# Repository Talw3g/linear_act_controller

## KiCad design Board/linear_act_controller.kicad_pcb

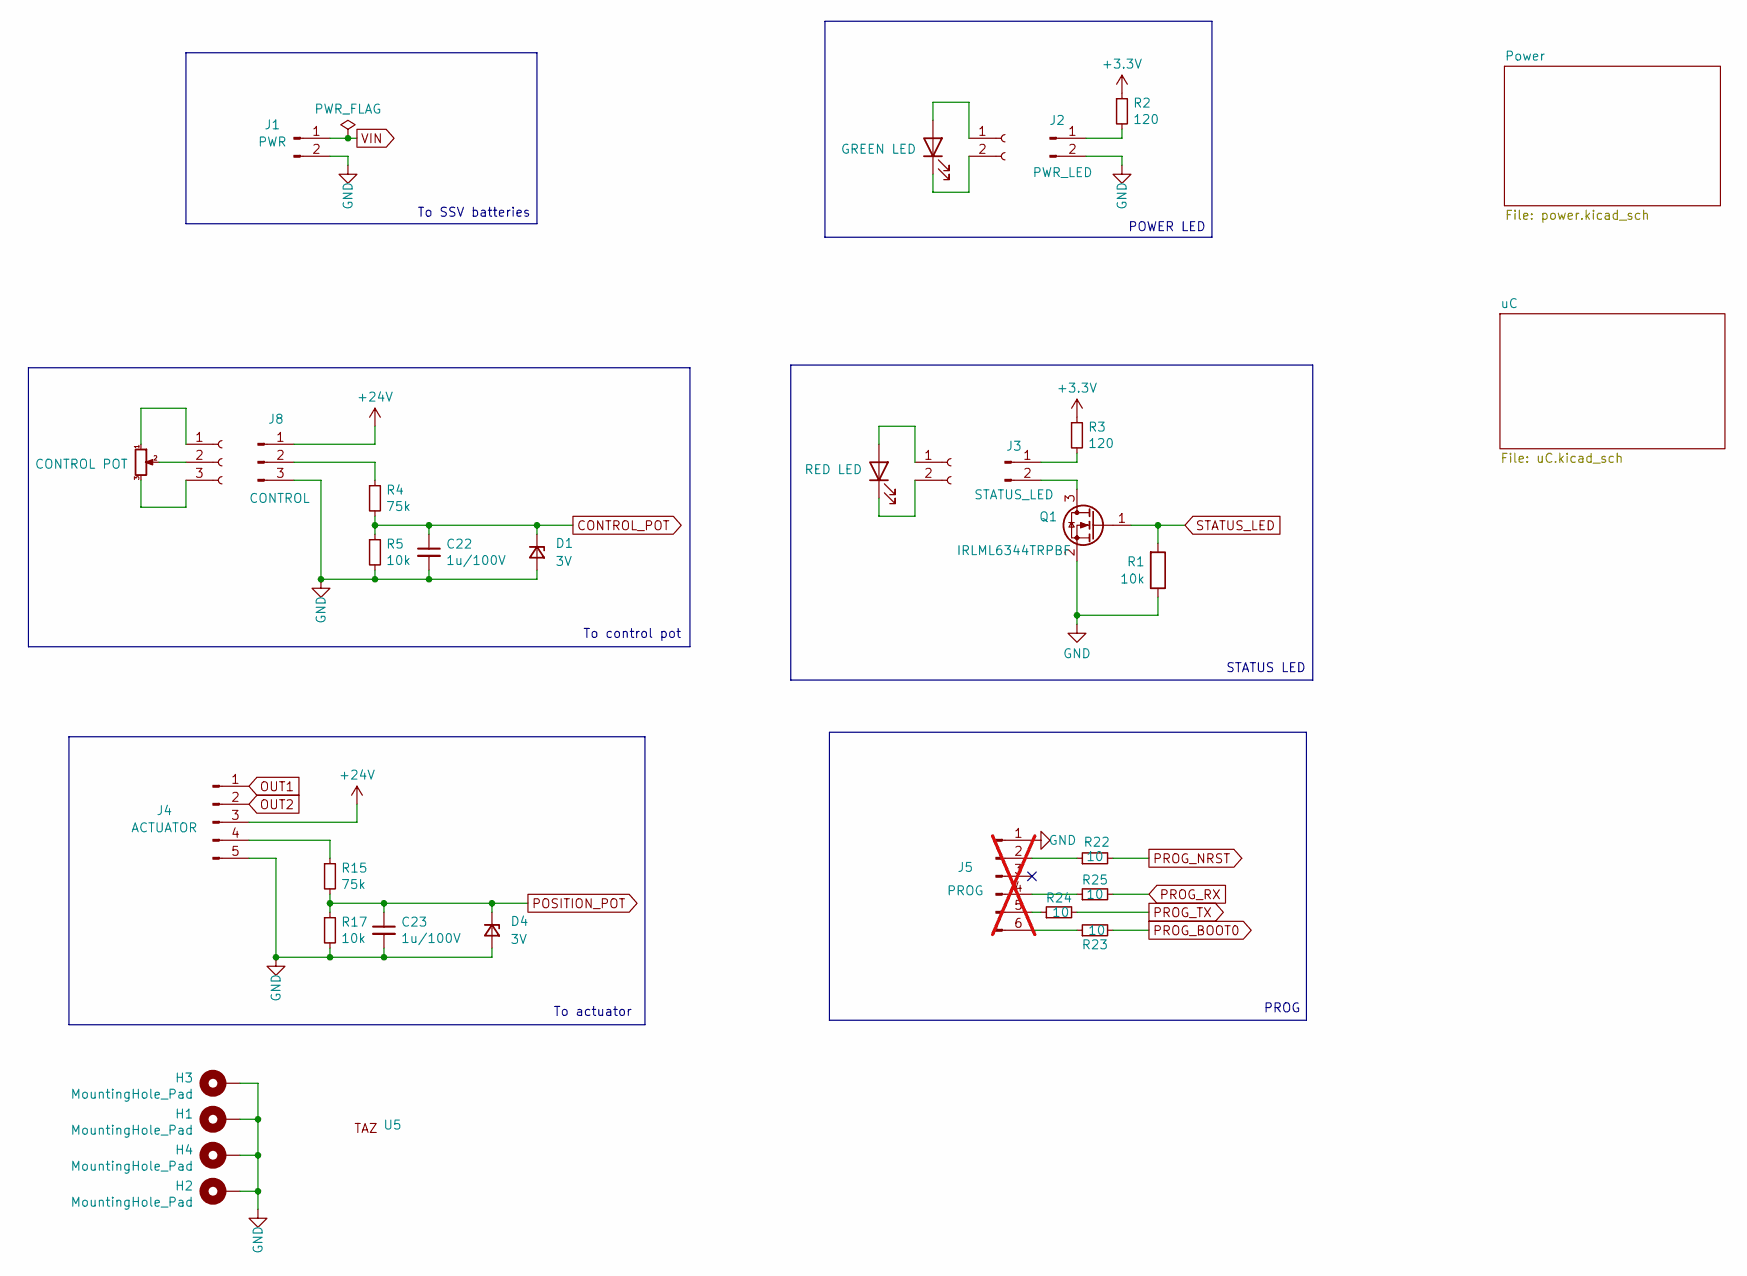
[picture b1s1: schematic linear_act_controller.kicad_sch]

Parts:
C22, C23: 1u/100V; C_0603_1608Metric_Pad1.08x0.95mm_HandSolder
D1, D4: 3V; D_SOD-323_HandSoldering
D6: GREEN LED
D7: RED LED
H1, H2, H3, H4: MountingHole_Pad; MountingHole_3.5mm_Pad_Via
J1: PWR; JST_XH_B2B-XH-A_1x02_P2.50mm_Vertical
J2: PWR_LED; JST_XH_B2B-XH-A_1x02_P2.50mm_Vertical
J3: STATUS_LED; JST_XH_B2B-XH-A_1x02_P2.50mm_Vertical
J4: ACTUATOR; JST_XH_B5B-XH-A_1x05_P2.50mm_Vertical
J5: PROG; 6pins_prog_header; not fitted
J6, J7: PWR_LED
J8: CONTROL; JST_XH_B3B-XH-A_1x03_P2.50mm_Vertical
J9: Conn_01x03_Socket
Q1: IRLML6344TRPBF; SOT-23
R1, R5, R17: 10k; R_0603_1608Metric_Pad0.98x0.95mm_HandSolder
R2, R3: 120; R_0603_1608Metric_Pad0.98x0.95mm_HandSolder
R4, R15: 75k; R_0603_1608Metric_Pad0.98x0.95mm_HandSolder
R22, R23, R24, R25: 10; R_0603_1608Metric_Pad0.98x0.95mm_HandSolder
RV1: CONTROL POT
U5: taz

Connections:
+3.3V: R2.1, R3.1; also elsewhere on the board
+24V: J4.3, J8.1; also elsewhere on the board
CONTROL_POT: C22.1, D1.1 (K), R4.2, R5.1; also elsewhere on the board
GND: C22.2, C23.2, D1.2 (A), D4.2 (A), H1.1, H2.1, H3.1, H4.1, J1.2, J2.2, J4.5, J5.1, J8.3, Q1.2 (S), R1.1, R5.2, R17.2; also elsewhere on the board
unnamed: D6.1 (K), J6.2
unnamed: D6.2 (A), J6.1
unnamed: D7.1 (K), J7.2
unnamed: D7.2 (A), J7.1
unnamed: J2.1, R2.2
unnamed: J3.1, R3.2
unnamed: J3.2, Q1.3 (D)
unnamed: J4.4, R15.1
unnamed: J5.2, R22.1
unnamed: J5.4, R25.1
unnamed: J5.5, R24.1
unnamed: J5.6, R23.1
unnamed: J8.2, R4.1
unnamed: J9.1, RV1.1
unnamed: J9.2, RV1.2
unnamed: J9.3, RV1.3
OUT1: J4.1; also elsewhere on the board
OUT2: J4.2; also elsewhere on the board
POSITION_POT: C23.1, D4.1 (K), R15.2, R17.1; also elsewhere on the board
PROG_BOOT0: R23.2; also elsewhere on the board
PROG_NRST: R22.2; also elsewhere on the board
PROG_RX: R25.2; also elsewhere on the board
PROG_TX: R24.2; also elsewhere on the board
STATUS_LED: Q1.1 (G), R1.2; also elsewhere on the board
VIN: J1.1; also elsewhere on the board

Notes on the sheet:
To control pot
STATUS LED
To actuator
To SSV batteries
POWER LED
PROG

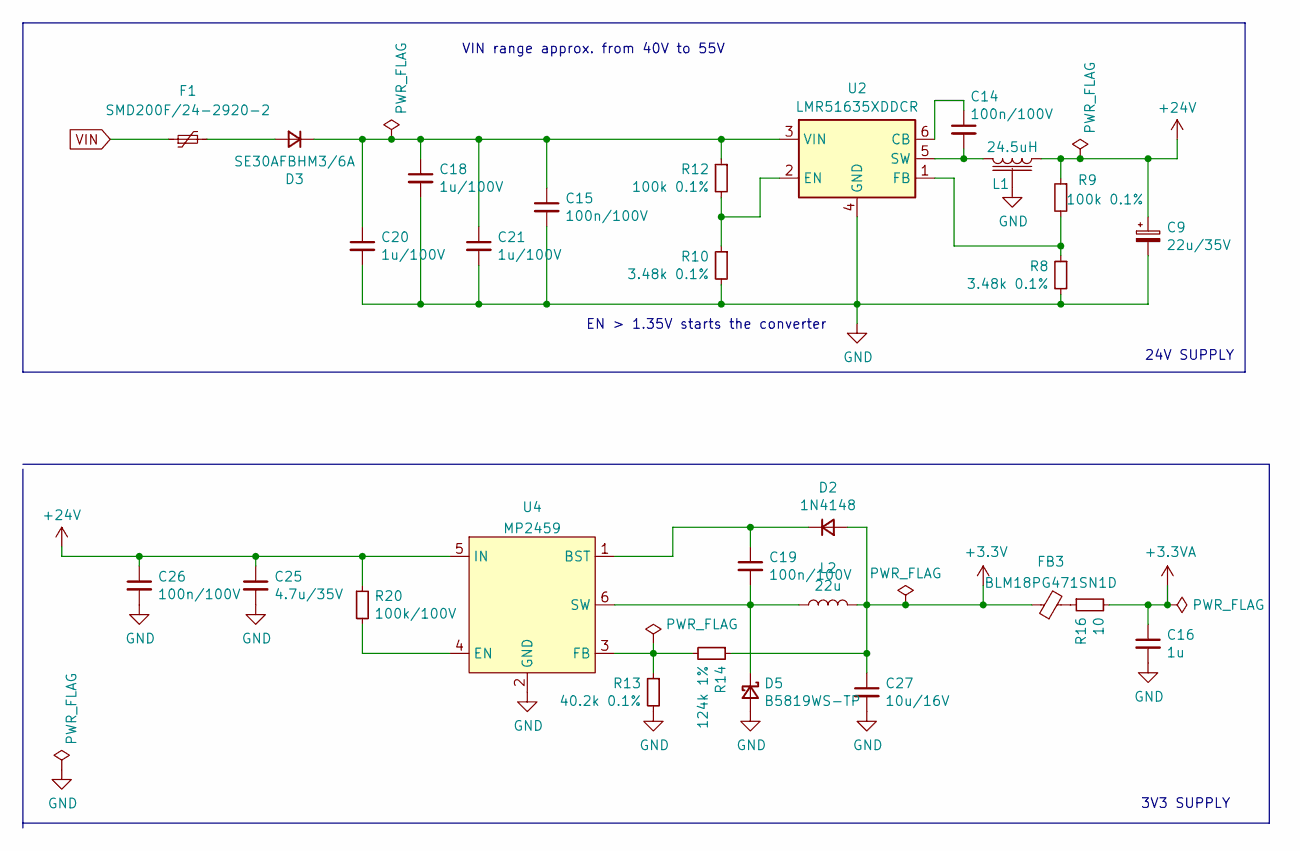
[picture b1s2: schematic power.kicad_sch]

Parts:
C9: 22u/35V; CP_Elec_6.3x5.8
C14, C15, C19, C26: 100n/100V; C_0603_1608Metric_Pad1.08x0.95mm_HandSolder
C16: 1u; C_0603_1608Metric_Pad1.08x0.95mm_HandSolder
C18, C20, C21: 1u/100V; C_0603_1608Metric_Pad1.08x0.95mm_HandSolder
C25: 4.7u/35V; C_0603_1608Metric_Pad1.08x0.95mm_HandSolder; JLCPCB C385986
C27: 10u/16V; C_0805_2012Metric_Pad1.18x1.45mm_HandSolder; JLCPCB C268007
D2: 1N4148; D_SOD-323_HandSoldering
D3: SE30AFBHM3/6A; D_SMA_Handsoldering; JLCPCB C64898
D5: B5819WS-TP; D_SOD-323_HandSoldering
F1: SMD200F/24-2920-2; Fuse_2920_7451Metric_Pad2.10x5.45mm_HandSolder
FB3: BLM18PG471SN1D; L_0603_1608Metric_Pad1.05x0.95mm_HandSolder
L1: 24.5uH; Pulse_PG1083.253NLT; JLCPCB C136260
L2: 22u; L_1008_2520Metric_Pad1.43x2.20mm_HandSolder; JLCPCB C136260
R8, R10: 3.48k 0.1%; R_0603_1608Metric_Pad0.98x0.95mm_HandSolder
R9, R12: 100k 0.1%; R_0603_1608Metric_Pad0.98x0.95mm_HandSolder
R13: 40.2k 0.1%; R_0603_1608Metric_Pad0.98x0.95mm_HandSolder
R14: 124k 1%; R_0603_1608Metric_Pad0.98x0.95mm_HandSolder
R16: 10; R_0603_1608Metric_Pad0.98x0.95mm_HandSolder
R20: 100k/100V; R_0603_1608Metric_Pad0.98x0.95mm_HandSolder
U2: LMR51635XDDCR; SOT-23-6
U4: MP2459; TSOT-23-6

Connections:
+3.3V: C27.1, D2.2 (A), FB3.1, L2.2, R14.1; also elsewhere on the board
+3.3VA: C16.1, R16.2; also elsewhere on the board
+24V: C9.1, C25.1, C26.1, L1.1, R9.1, R20.1, U4.5 (IN); also elsewhere on the board
GND: C9.2, C15.2, C16.2, C18.2, C20.2, C21.2, C25.2, C26.2, C27.2, D5.2 (A), L1.3 (case), R8.2, R10.2, R13.2, U2.4 (GND), U4.2 (GND); also elsewhere on the board
unnamed: C19.1, D2.1 (K), U4.1 (BST)
unnamed: D3.2 (A), F1.2
unnamed: C15.1, C18.1, C20.1, C21.1, D3.1 (K), R12.1, U2.3 (VIN)
unnamed: C19.2, D5.1 (K), L2.1, U4.6 (SW)
unnamed: FB3.2, R16.1
unnamed: C14.1, U2.6 (CB)
unnamed: R10.1, R12.2, U2.2 (EN)
unnamed: R8.1, R9.2, U2.1 (FB)
unnamed: C14.2, L1.2, U2.5 (SW)
unnamed: R20.2, U4.4 (EN)
unnamed: R13.1, R14.2, U4.3 (FB)
VIN: F1.1; also elsewhere on the board

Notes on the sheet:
EN > 1.35V starts the converter
3V3 SUPPLY
24V SUPPLY
VIN range approx. from 40V to 55V

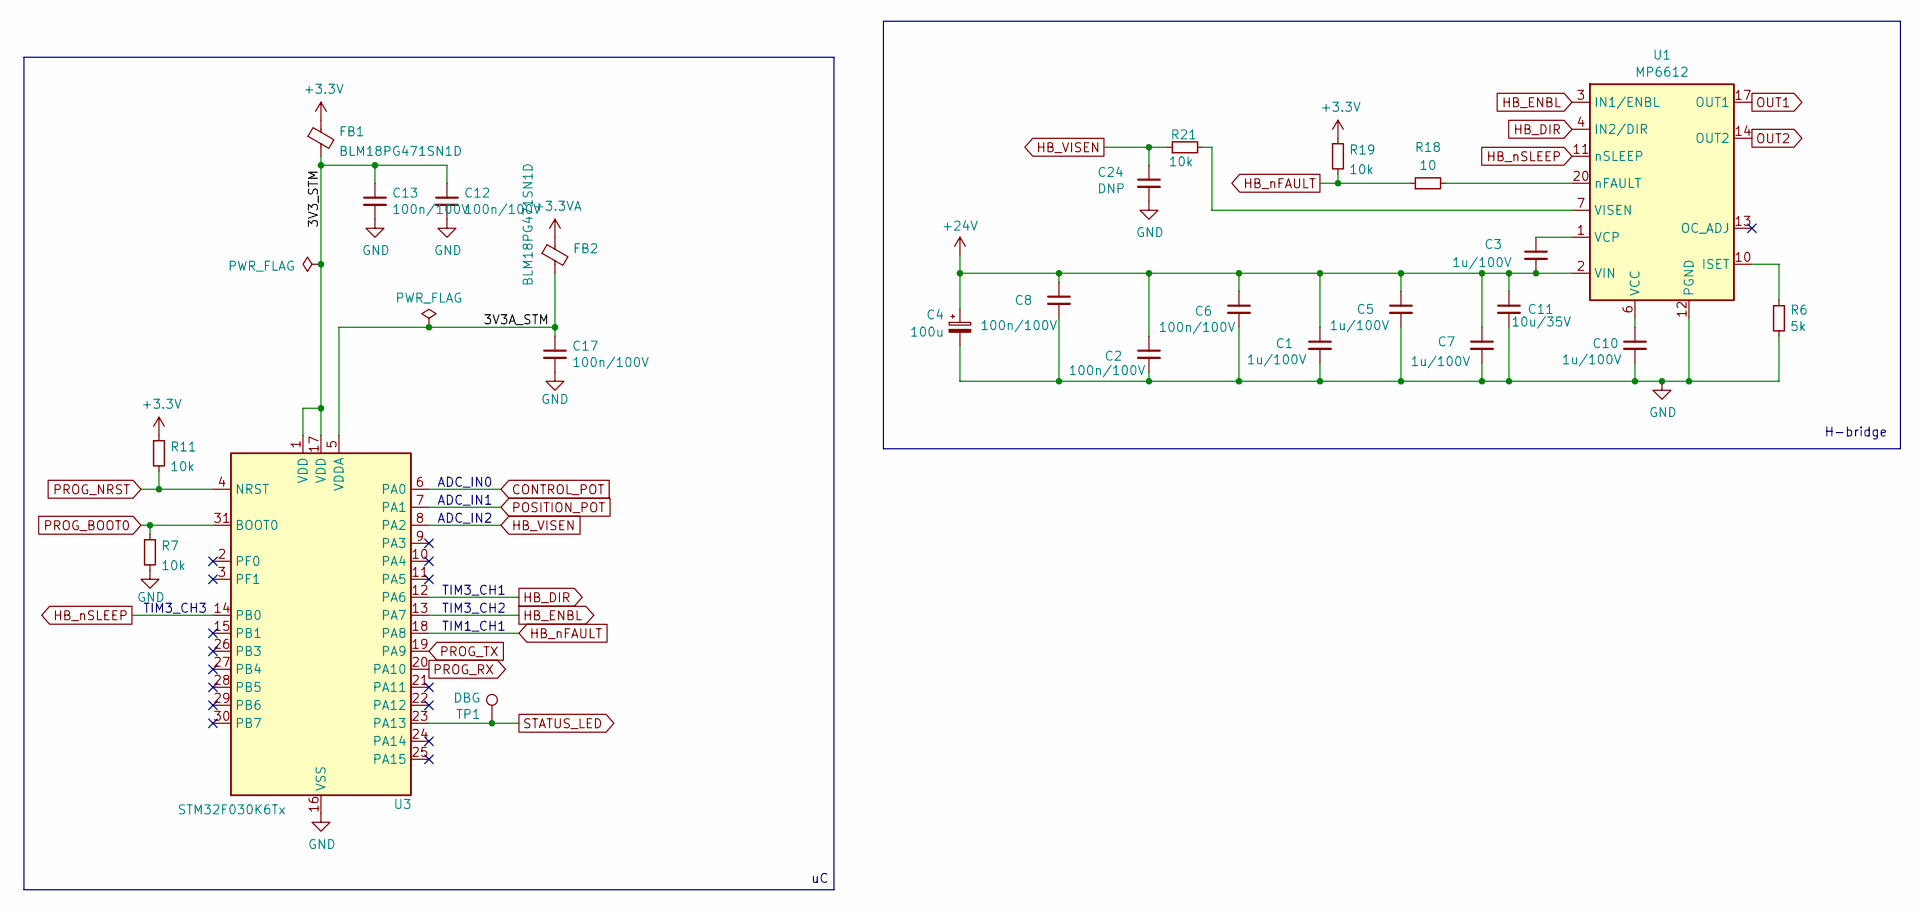
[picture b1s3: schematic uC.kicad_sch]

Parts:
C1, C3, C5, C7, C10: 1u/100V; C_0603_1608Metric_Pad1.08x0.95mm_HandSolder
C2, C6, C8, C12, C13, C17: 100n/100V; C_0603_1608Metric_Pad1.08x0.95mm_HandSolder
C4: 100u; CP_Elec_8x10
C11: 10u/35V; C_0603_1608Metric_Pad1.08x0.95mm_HandSolder
C24: DNP; C_0603_1608Metric_Pad1.08x0.95mm_HandSolder
FB1, FB2: BLM18PG471SN1D; L_0603_1608Metric_Pad1.05x0.95mm_HandSolder
R6: 5k; R_0603_1608Metric_Pad0.98x0.95mm_HandSolder
R7, R11, R19, R21: 10k; R_0603_1608Metric_Pad0.98x0.95mm_HandSolder
R18: 10; R_0603_1608Metric_Pad0.98x0.95mm_HandSolder
TP1: DBG; TestPoint_Pad_D1.0mm
U1: MP6612; TSSOP-20-1EP_4.4x6.5mm_P0.65mm_handsolder
U3: STM32F030K6Tx; LQFP-32_7x7mm_P0.8mm

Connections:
+3.3V: FB1.1, R11.1, R19.1; also elsewhere on the board
+3.3VA: FB2.1; also elsewhere on the board
+24V: C1.1, C2.1, C3.2, C4.1, C5.1, C6.1, C7.1, C8.1, C11.1, U1.2 (VIN), U1.5 (VIN), U1.9 (VIN); also elsewhere on the board
/uC/3V3A_STM: C17.1, FB2.2, U3.5 (VDDA)
/uC/3V3_STM: C12.1, C13.1, FB1.2, U3.1 (VDD), U3.17 (VDD)
CONTROL_POT: U3.6 (PA0); also elsewhere on the board
GND: C1.2, C2.2, C4.2, C5.2, C6.2, C7.2, C8.2, C10.2, C11.2, C12.2, C13.2, C17.2, C24.2, R6.2, R7.2, U1.8 (AGND), U1.12 (PGND), U1.16 (PGND), U1.19 (PGND), U1.21 (PGND), U3.16 (VSS), U3.32 (VSS); also elsewhere on the board
HB_DIR: U1.4 (IN2/DIR), U3.12 (PA6)
HB_ENBL: U1.3 (IN1/ENBL), U3.13 (PA7)
HB_VISEN: C24.1, R21.1, U3.8 (PA2)
HB_nFAULT: R18.1, R19.2, U3.18 (PA8)
HB_nSLEEP: U1.11 (nSLEEP), U3.14 (PB0)
unnamed: R6.1, U1.10 (ISET)
unnamed: C10.1, U1.6 (VCC)
unnamed: C3.1, U1.1 (VCP)
unnamed: R21.2, U1.7 (VISEN)
unnamed: R18.2, U1.20 (nFAULT)
OUT1: U1.17 (OUT1), U1.18 (OUT1); also elsewhere on the board
OUT2: U1.14 (OUT2), U1.15 (OUT2); also elsewhere on the board
POSITION_POT: U3.7 (PA1); also elsewhere on the board
PROG_BOOT0: R7.1, U3.31 (BOOT0); also elsewhere on the board
PROG_NRST: R11.2, U3.4 (NRST); also elsewhere on the board
PROG_RX: U3.20 (PA10); also elsewhere on the board
PROG_TX: U3.19 (PA9); also elsewhere on the board
STATUS_LED: TP1.1, U3.23 (PA13); also elsewhere on the board

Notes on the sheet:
H-bridge
TIM3_CH1
TIM3_CH2
TIM1_CH1
ADC_IN1
TIM3_CH3
ADC_IN0
ADC_IN2

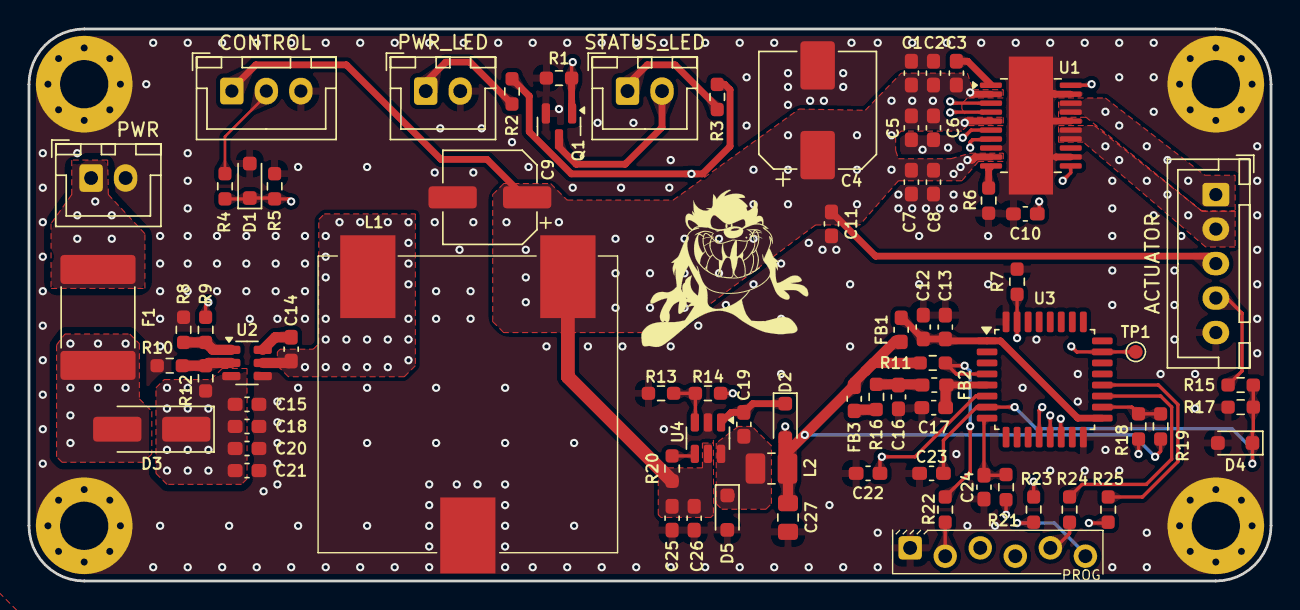
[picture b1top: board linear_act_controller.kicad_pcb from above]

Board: 4 copper layers, 90.0 x 40.0 mm, 80 parts (0 on the bottom side), 46 nets.

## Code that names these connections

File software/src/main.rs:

#![no_main]
#![no_std]

// Setup startup code and minimal runtime for uC
// (check https://docs.rs/cortex-m-rt/latest/cortex_m_rt/)
use cortex_m_rt::entry;

use stm32f0xx_hal::{adc, pac, prelude::*, pwm, serial};

use heapless::spsc::Queue;

use core::fmt::Write;

use core::panic::PanicInfo;
#[panic_handler]
fn panic(_pi: &PanicInfo) -> ! {
    cortex_m::asm::delay(10_000_000);
    // reboot in bootloader mode
    cortex_m::peripheral::SCB::sys_reset();
}
const AVG_RANGE: usize = 50; // number of values for avg
const POS_MAX_MV: u16 = 295; // mv reading when actuator fully extended
const POS_MIN_MV: u16 = 1830; // mv reading when actuator fully retracted
const CTRL_MIN_MV: u16 = 0; // mv reading when pot at 0%
const CTRL_MAX_MV: u16 = 2834; // mv reading when pot at 100%
const POS_MAX_ERR: f32 = 5.0; // pos error (%) for full speed
const POS_MIN_ERR: f32 = 0.5; // authorized pos error (%)
const I_LIMIT: u16 = 2; // current limit (A)
const I_LIMIT_MV: u16 = I_LIMIT * 500; // current limit in mV (500mV = 1A)
const MIN_SPEED: f32 = 100.0;
const MAX_SPEED: f32 = 480.0;

#[entry]
fn main() -> ! {
    // -- CONFIG --

    let mut p = pac::Peripherals::take().unwrap();
    let mut _cp = cortex_m::peripheral::Peripherals::take().unwrap();

    // when booting from bootloader memory mapping will have
    // System Flash memory (bootloader code) mapped at 0x0000_0000
    // resulting in bootloader interrupt vectors to be used
    // The following line will force memory mapping to Main Flash memory
    // as intended by this code
    p.SYSCFG.cfgr1.modify(|_, w| w.mem_mode().main_flash());

    // configure clock frequency
    let mut rcc = p.RCC.configure().sysclk(48.mhz()).freeze(&mut p.FLASH);

    let gpioa = p.GPIOA.split(&mut rcc);
    let gpiob = p.GPIOB.split(&mut rcc);
    let _gpiof = p.GPIOF.split(&mut rcc);

    // -- GPIOs --
    // status led:
    let mut led = cortex_m::interrupt::free(|cs| gpioa.pa13.into_push_pull_output(cs));
    // halfbridge direction:
    let mut hb_dir = cortex_m::interrupt::free(|cs| gpioa.pa6.into_push_pull_output(cs));
    // halfbridge nsleep (needs to be pulled high to operate):
    let mut hb_nsleep = cortex_m::interrupt::free(|cs| gpiob.pb0.into_push_pull_output(cs));
    hb_nsleep.set_high().ok();
    let hb_nfault = cortex_m::interrupt::free(|cs| gpioa.pa8.into_floating_input(cs));

    // -- DEBUG SERIAL LINK --
    // configure debug serial link
    let mut s = cortex_m::interrupt::free(|cs| {
        let tx = gpioa.pa9.into_alternate_af1(cs);
        let rx = gpioa.pa10.into_alternate_af1(cs);
        serial::Serial::usart1(p.USART1, (tx, rx), 115200.bps(), &mut rcc)
    });
    write!(s, "BOOTING").ok();

    // -- ADCs --
    let mut adc = adc::Adc::new(p.ADC, &mut rcc);
    // control potentiometer:
    let mut ctrl_pot_pin = cortex_m::interrupt::free(|cs| gpioa.pa0.into_analog(cs));
    // actuator position potentiometer:
    let mut pos_pot_pin = cortex_m::interrupt::free(|cs| gpioa.pa1.into_analog(cs));
    // halfbridge current sensor output:
    let mut visen_pin = cortex_m::interrupt::free(|cs| gpioa.pa2.into_analog(cs));

    // -- PWMs --
    // halfbridge enable control:
    let hb_enbl_pwm_pin = cortex_m::interrupt::free(|cs| gpioa.pa7.into_alternate_af1(cs));
    let mut hb_enbl_pwm = pwm::tim3(p.TIM3, hb_enbl_pwm_pin, &mut rcc, 100.khz());
    hb_enbl_pwm.enable();

    // -- QUEUES --
    let mut ctrl_pot_queue: Queue<u16, AVG_RANGE> = Queue::new();
    let mut pos_pot_queue: Queue<u16, AVG_RANGE> = Queue::new();
    let mut visen_queue: Queue<u16, AVG_RANGE> = Queue::new();

    let mut i: u16 = 0;
    loop {
        i += 1;
        // measure voltages on ADC
        let visen: u16 = adc.read_abs_mv(&mut visen_pin);
        visen_queue.enqueue(visen).ok();
        let ctrl_pot: u16 = adc.read_abs_mv(&mut ctrl_pot_pin);
        ctrl_pot_queue.enqueue(ctrl_pot).ok();
        let pos_pot: u16 = adc.read_abs_mv(&mut pos_pot_pin);
        pos_pot_queue.enqueue(pos_pot).ok();

        // warn user if halfbridge fault:
        if Ok(true) == hb_nfault.is_low() {
            writeln!(s, "Halfbridge fault detected").ok();
            if i.is_multiple_of(50) {
                led.toggle().ok();
                i = 0;
            }
            continue;
        }
        // software current limitation:
        if mean(&visen_queue) > I_LIMIT_MV {
            writeln!(s, "Triggered current limit: {visen}").ok();
            hb_enbl_pwm.set_duty(0);
            if i.is_multiple_of(150) {
                led.toggle().ok();
                i = 0;
            }
            continue;
        }

        // Wait for queues to be full:
        if !(ctrl_pot_queue.is_full() & pos_pot_queue.is_full()) {
            continue;
        }

        let _ctrl = mean(&ctrl_pot_queue);
        let _pos = mean(&pos_pot_queue);
        let ctrl: f32 =
            (_ctrl as f32 - CTRL_MIN_MV as f32) / (CTRL_MAX_MV as f32 - CTRL_MIN_MV as f32) * 100.0;
        let pos: f32 =
            (_pos as f32 - POS_MIN_MV as f32) / (POS_MAX_MV as f32 - POS_MIN_MV as f32) * 100.0;
        let pos_err = pos - ctrl;
        let speed = ((pos_err.abs() * MAX_SPEED / POS_MAX_ERR).clamp(MIN_SPEED, MAX_SPEED)) as u16;

        if pos_err.abs() <= POS_MIN_ERR {
            // target reached
            hb_enbl_pwm.set_duty(0);
            led.set_low().ok();
        } else {
            if pos_err < 0.0 {
                // below target
                hb_dir.set_high().ok();
            } else {
                // above target
                hb_dir.set_low().ok();
            }
            hb_enbl_pwm.set_duty(speed);
            led.set_high().ok();
        }

        let _ = ctrl_pot_queue.dequeue();
        let _ = pos_pot_queue.dequeue();
        if i > 65_000 {
            i = 0;
        }
        // wait some time
        cortex_m::asm::delay(10_000);
    }
}

fn sum(queue: &Queue<u16, AVG_RANGE>) -> u32 {
    let mut s: u32 = 0;
    for val in queue.iter() {
        s += *val as u32;
    }
    s
}

fn mean(queue: &Queue<u16, AVG_RANGE>) -> u16 {
    (sum(queue) / (queue.len() as u32)) as u16
}

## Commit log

2025-06-16 Routing mostly done
2025-06-18 Schematic done.
2025-06-24 Included jdam's improvements.
2025-06-28 WIP on routing
2025-06-29 Routing done, before adding polyfuse
2025-07-03 Routing done with polyfuse. Need to tidy silkscreen.
2025-07-03 Silkscreen done.
2025-07-06 some 24V and GND traces to H bridge enlarged
2025-07-21 Changed some components based on availability.
2025-07-22 Split "SSV" connector into "PWR" and "CONTROL"
2025-08-25 Updated prog header with increased dealignment
2025-10-20 Added JDRobotter code sample
2025-10-22 WIP on position control
2025-10-24 Control done
2025-11-13 Small tweaks with real actuator
